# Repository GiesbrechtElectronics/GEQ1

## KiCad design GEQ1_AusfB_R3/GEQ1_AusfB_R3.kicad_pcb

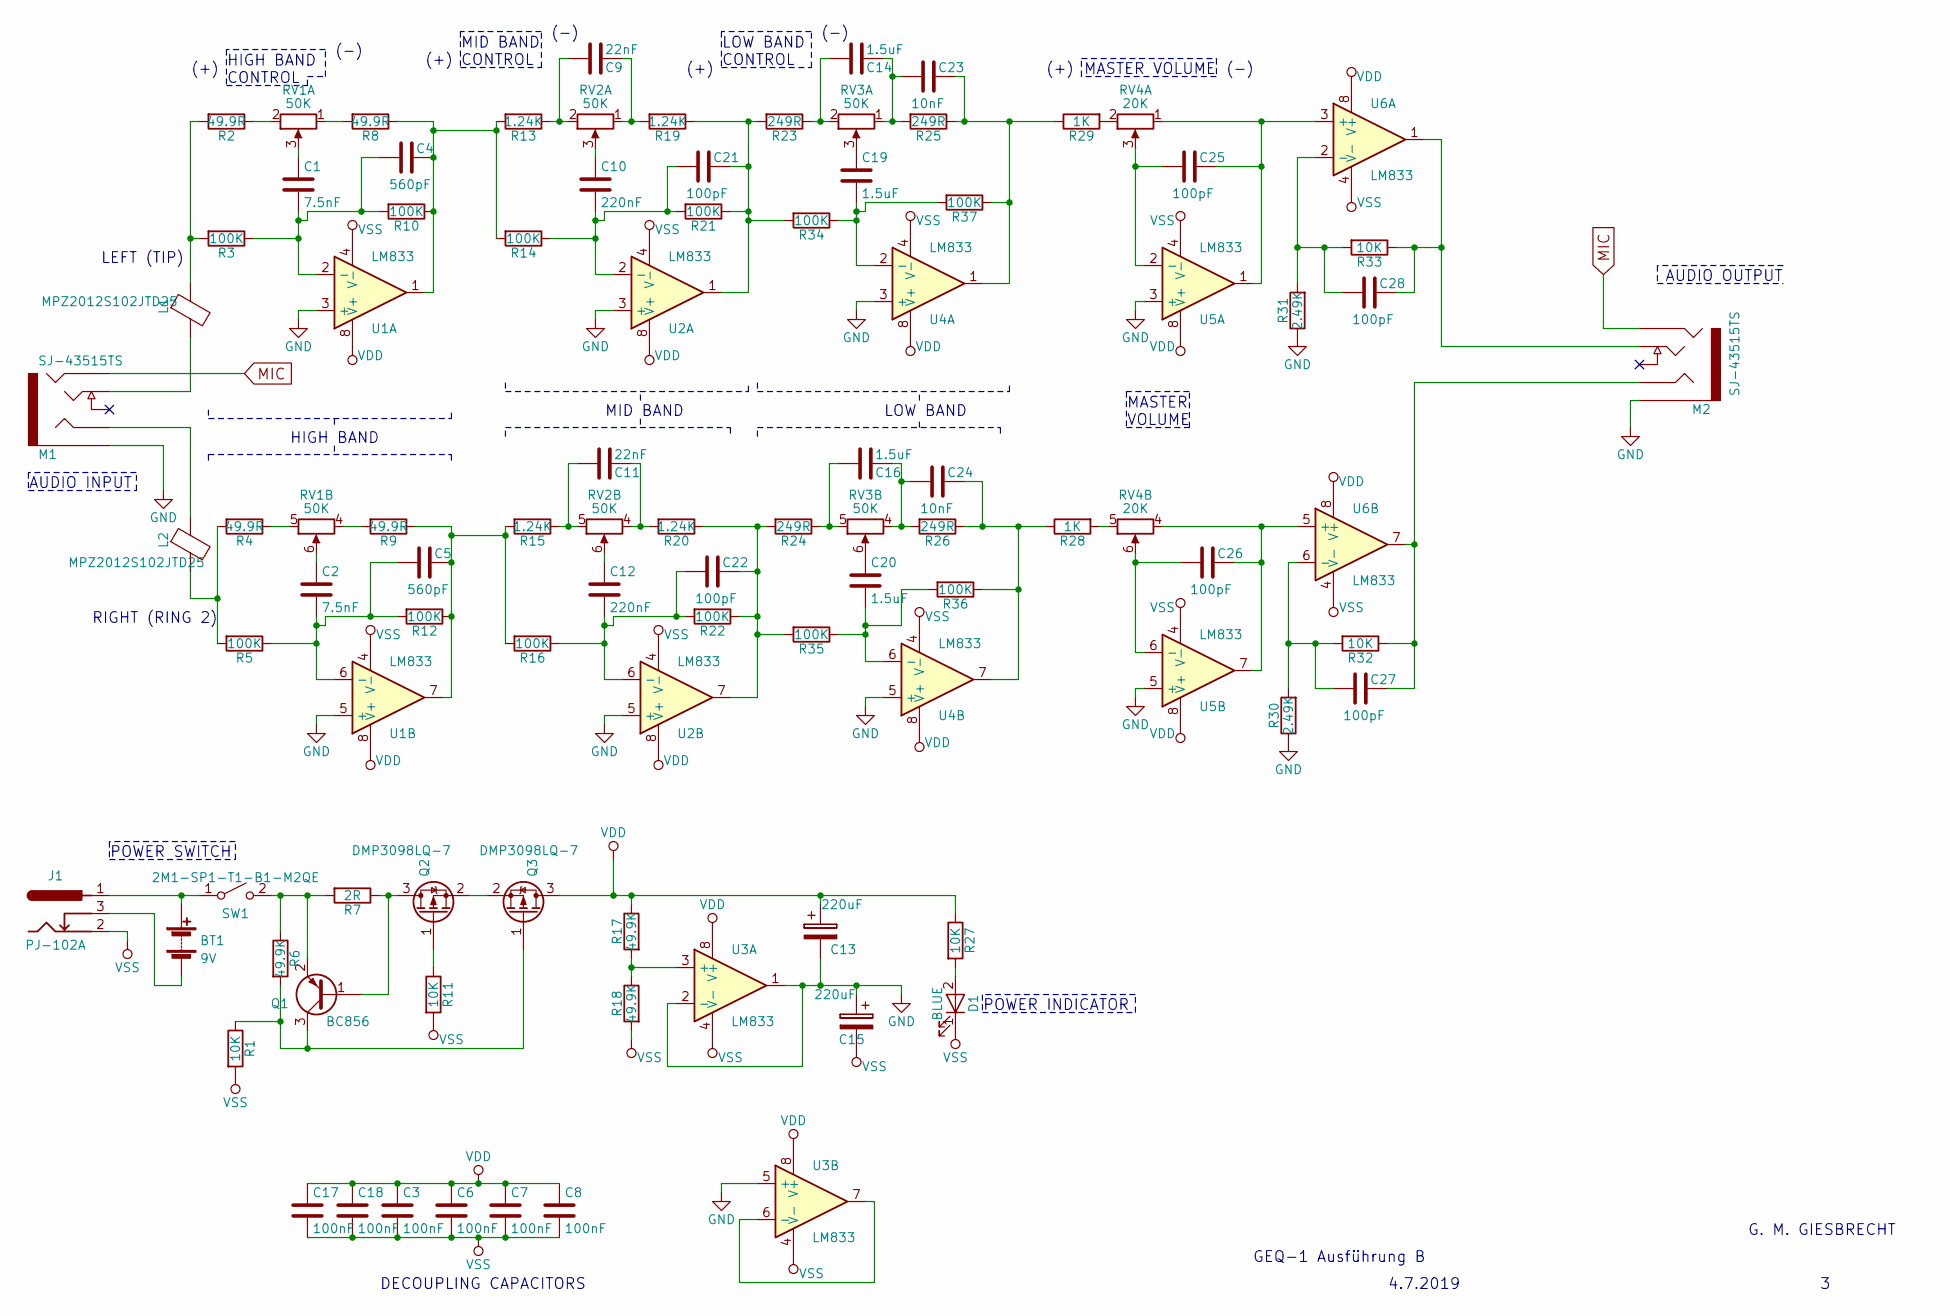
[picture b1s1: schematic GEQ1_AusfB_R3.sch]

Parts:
BT1: 9V; 2_Pin_Header
C1, C2: 7.5nF; C_0805
C3, C6, C7, C8, C17, C18: 100nF; C_0805
C4, C5: 560pF; C_0805
C9, C11: 22nF; C_0805
C10, C12: 220nF; C_0805
C13, C15: 220uF; CP_Elec_8x10
C14, C16, C19, C20: 1.5uF; C_0805
C21, C22, C25, C26, C27, C28: 100pF; C_0805
C23, C24: 10nF; C_0805
D1: BLUE; LED_1206_REV
J1: PJ-102A; PJ_102A
L1, L2: MPZ2012S102JTD25; L_0805
M1, M2: SJ-43515TS; TRRS_SJ-43515TS
Q1: BC856; SOT-23_Handsoldering
Q2, Q3: DMP3098LQ-7; SOT-23
R1, R11, R27, R32, R33: 10K; R_0805
R2, R4, R8, R9: 49.9R; R_0805
R3, R5, R10, R12, R14, R16, R21, R22, R34, R35, R36, R37: 100K; R_0805
R6, R17, R18: 49.9K; R_0805
R7: 2R; R_0805
R13, R15, R19, R20: 1.24K; R_0805
R23, R24, R25, R26: 249R; R_0805
R28, R29: 1K; R_0805
R30, R31: 2.49K; R_0805
RV1, RV2, RV3: 50K; POT_2GANG_RK12L
RV4: 20K; POT_2GANG_RK12L
SW1: 2M1-SP1-T1-B1-M2QE; 2M1-SP1-TnBnM2
U1, U2, U3, U4, U5, U6: LM833; SOIC-8_Pin1Line

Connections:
GND: C13.2, C15.1, M1.1 (SLEEVE), M2.1 (SLEEVE), R30.1, R31.1, U1.3 (+), U1.5 (+), U2.3 (+), U2.5 (+), U3.1, U3.2 (-), U3.5 (+), U4.3 (+), U4.5 (+), U5.3 (+), U5.5 (+)
MIC: M1.4 (RING2), M2.4 (RING2)
unnamed: BT1.1 (+), J1.1, SW1.1 (A)
unnamed: BT1.2 (-), J1.3
unnamed: C1.1, RV1.3 (6)
unnamed: C1.2, C4.2, R3.1, R10.2, U1.2 (-)
unnamed: C2.1, RV1.6
unnamed: C2.2, C5.2, R5.1, R12.2, U1.6 (-)
unnamed: C4.1, R8.1, R10.1, R13.2, R14.2, U1.1
unnamed: C5.1, R9.1, R12.1, R15.2, R16.2, U1.7
unnamed: C9.1, R19.2, RV2.1 (4)
unnamed: C9.2, R13.1, RV2.2 (5)
unnamed: C10.1, RV2.3 (6)
unnamed: C10.2, C21.2, R14.1, R21.2, U2.2 (-)
unnamed: C11.1, R20.2, RV2.4
unnamed: C11.2, R15.1, RV2.5
unnamed: C12.1, RV2.6
unnamed: C12.2, C22.2, R16.1, R22.2, U2.6 (-)
unnamed: C14.1, C23.2, R25.2, RV3.1 (4)
unnamed: C14.2, R23.1, RV3.2 (5)
unnamed: C16.1, C24.2, R26.2, RV3.4
unnamed: C16.2, R24.1, RV3.5
unnamed: C19.1, RV3.3 (6)
unnamed: C19.2, R34.1, R37.2, U4.2 (-)
unnamed: C20.1, RV3.6
unnamed: C20.2, R35.1, R36.2, U4.6 (-)
unnamed: C21.1, R19.1, R21.1, R23.2, R34.2, U2.1
unnamed: C22.1, R20.1, R22.1, R24.2, R35.2, U2.7
unnamed: C23.1, R25.1, R29.1, R37.1, U4.1
unnamed: C24.1, R26.1, R28.1, R36.1, U4.7
unnamed: C25.1, RV4.1 (4), U5.1, U6.3 (+)
unnamed: C25.2, RV4.3 (6), U5.2 (-)
unnamed: C26.1, RV4.4, U5.7, U6.5 (+)
unnamed: C26.2, RV4.6, U5.6 (-)
unnamed: C27.1, M2.3 (RING1), R32.1, U6.7
unnamed: C27.2, R30.2, R32.2, U6.6 (-)
unnamed: C28.1, M2.2 (TIP), R33.1, U6.1
unnamed: C28.2, R31.2, R33.2, U6.2 (-)
unnamed: D1.2 (A), R27.2
unnamed: L1.1, R2.2, R3.2
unnamed: L1.2, M1.2 (TIP)
unnamed: L2.1, M1.3 (RING1)
unnamed: L2.2, R4.2, R5.2
unnamed: Q1.1 (B), Q2.3 (D), R7.1
unnamed: Q1.2 (E), R6.1, R7.2, SW1.2 (B)
unnamed: Q1.3 (C), Q3.1 (G), R1.1, R6.2
unnamed: Q2.1 (G), R11.1
unnamed: Q2.2 (S), Q3.2 (S)
unnamed: R2.1, RV1.2 (5)
unnamed: R4.1, RV1.5
unnamed: R8.2, RV1.1 (4)
unnamed: R9.2, RV1.4
unnamed: R17.2, R18.1, U3.3 (+)
unnamed: R28.2, RV4.5
unnamed: R29.2, RV4.2 (5)
unnamed: U3.6 (-), U3.7
VDD: C3.1, C6.1, C7.1, C8.1, C13.1, C17.1, C18.1, Q3.3 (D), R17.1, R27.1, U1.8 (V+), U2.8 (V+), U3.8 (V+), U4.8 (V+), U5.8 (V+), U6.8 (V+)
VSS: C3.2, C6.2, C7.2, C8.2, C15.2, C17.2, C18.2, D1.1 (K), J1.2, R1.2, R11.2, R18.2, U1.4 (V-), U2.4 (V-), U3.4 (V-), U4.4 (V-), U5.4 (V-), U6.4 (V-)

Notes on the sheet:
LEFT (TIP)
RIGHT (RING 2)
LOW BAND
MID BAND
HIGH BAND
GEQ-1 Ausführung B
4.7.2019
G. M. GIESBRECHT
POWER INDICATOR
MASTER VOLUME
MID BAND CONTROL
LOW BAND CONTROL
HIGH BAND CONTROL
(-)
(+)
POWER SWITCH
AUDIO INPUT
AUDIO OUTPUT
DECOUPLING CAPACITORS
MASTER VOLUME

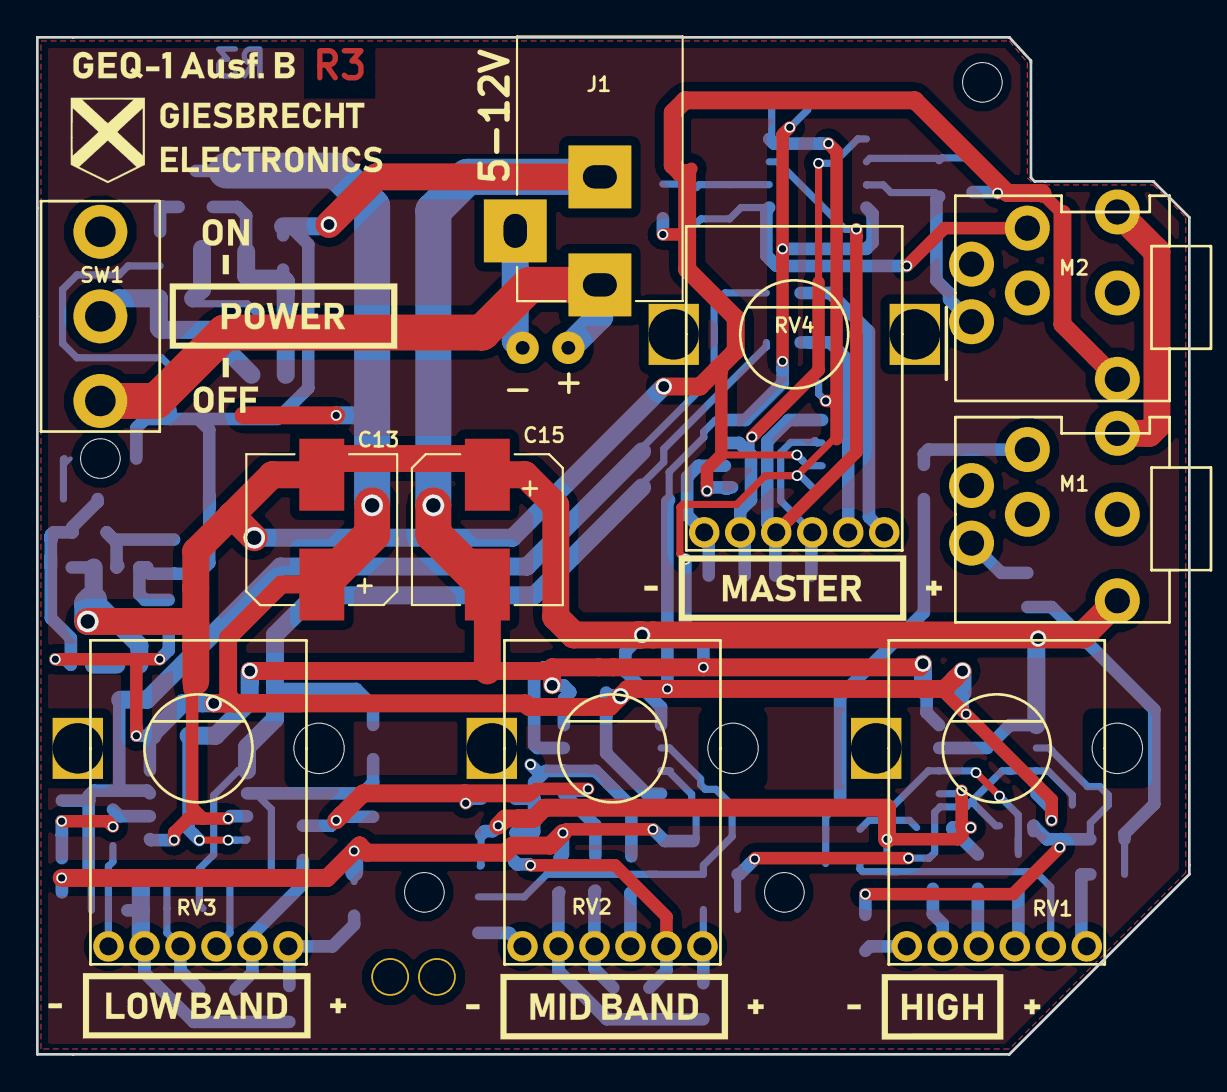
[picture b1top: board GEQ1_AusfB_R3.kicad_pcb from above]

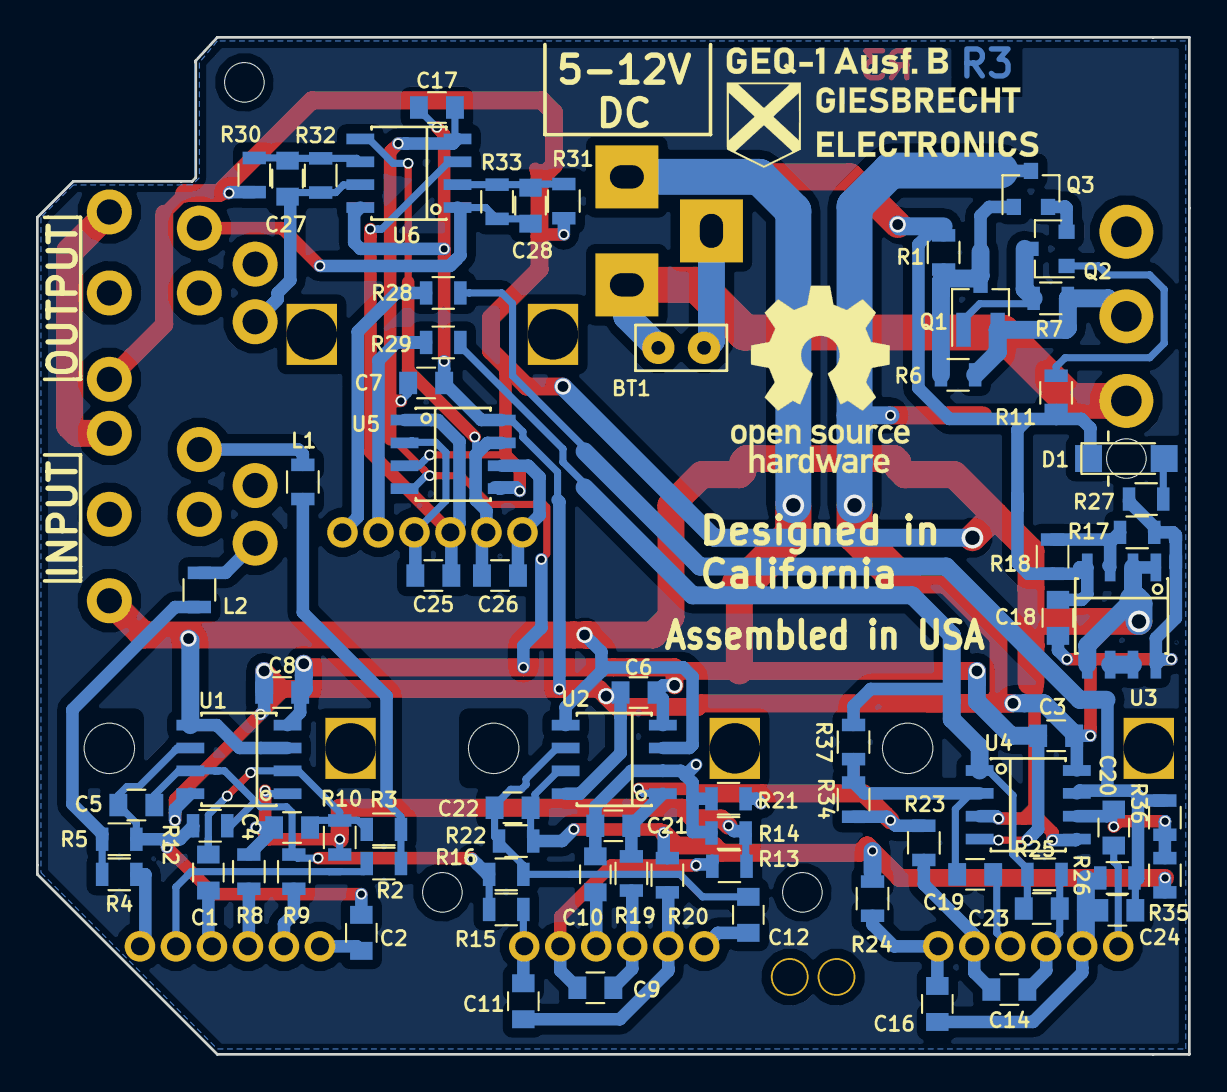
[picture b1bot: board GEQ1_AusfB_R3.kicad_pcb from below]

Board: 2 copper layers, 64.0 x 56.5 mm, 86 parts (76 on the bottom side), 58 nets.

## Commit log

2019-09-10 Commited GEQ1 AusfB R3
    Uploaded the original GEQ1 AusfB R3 KiCad project files.
